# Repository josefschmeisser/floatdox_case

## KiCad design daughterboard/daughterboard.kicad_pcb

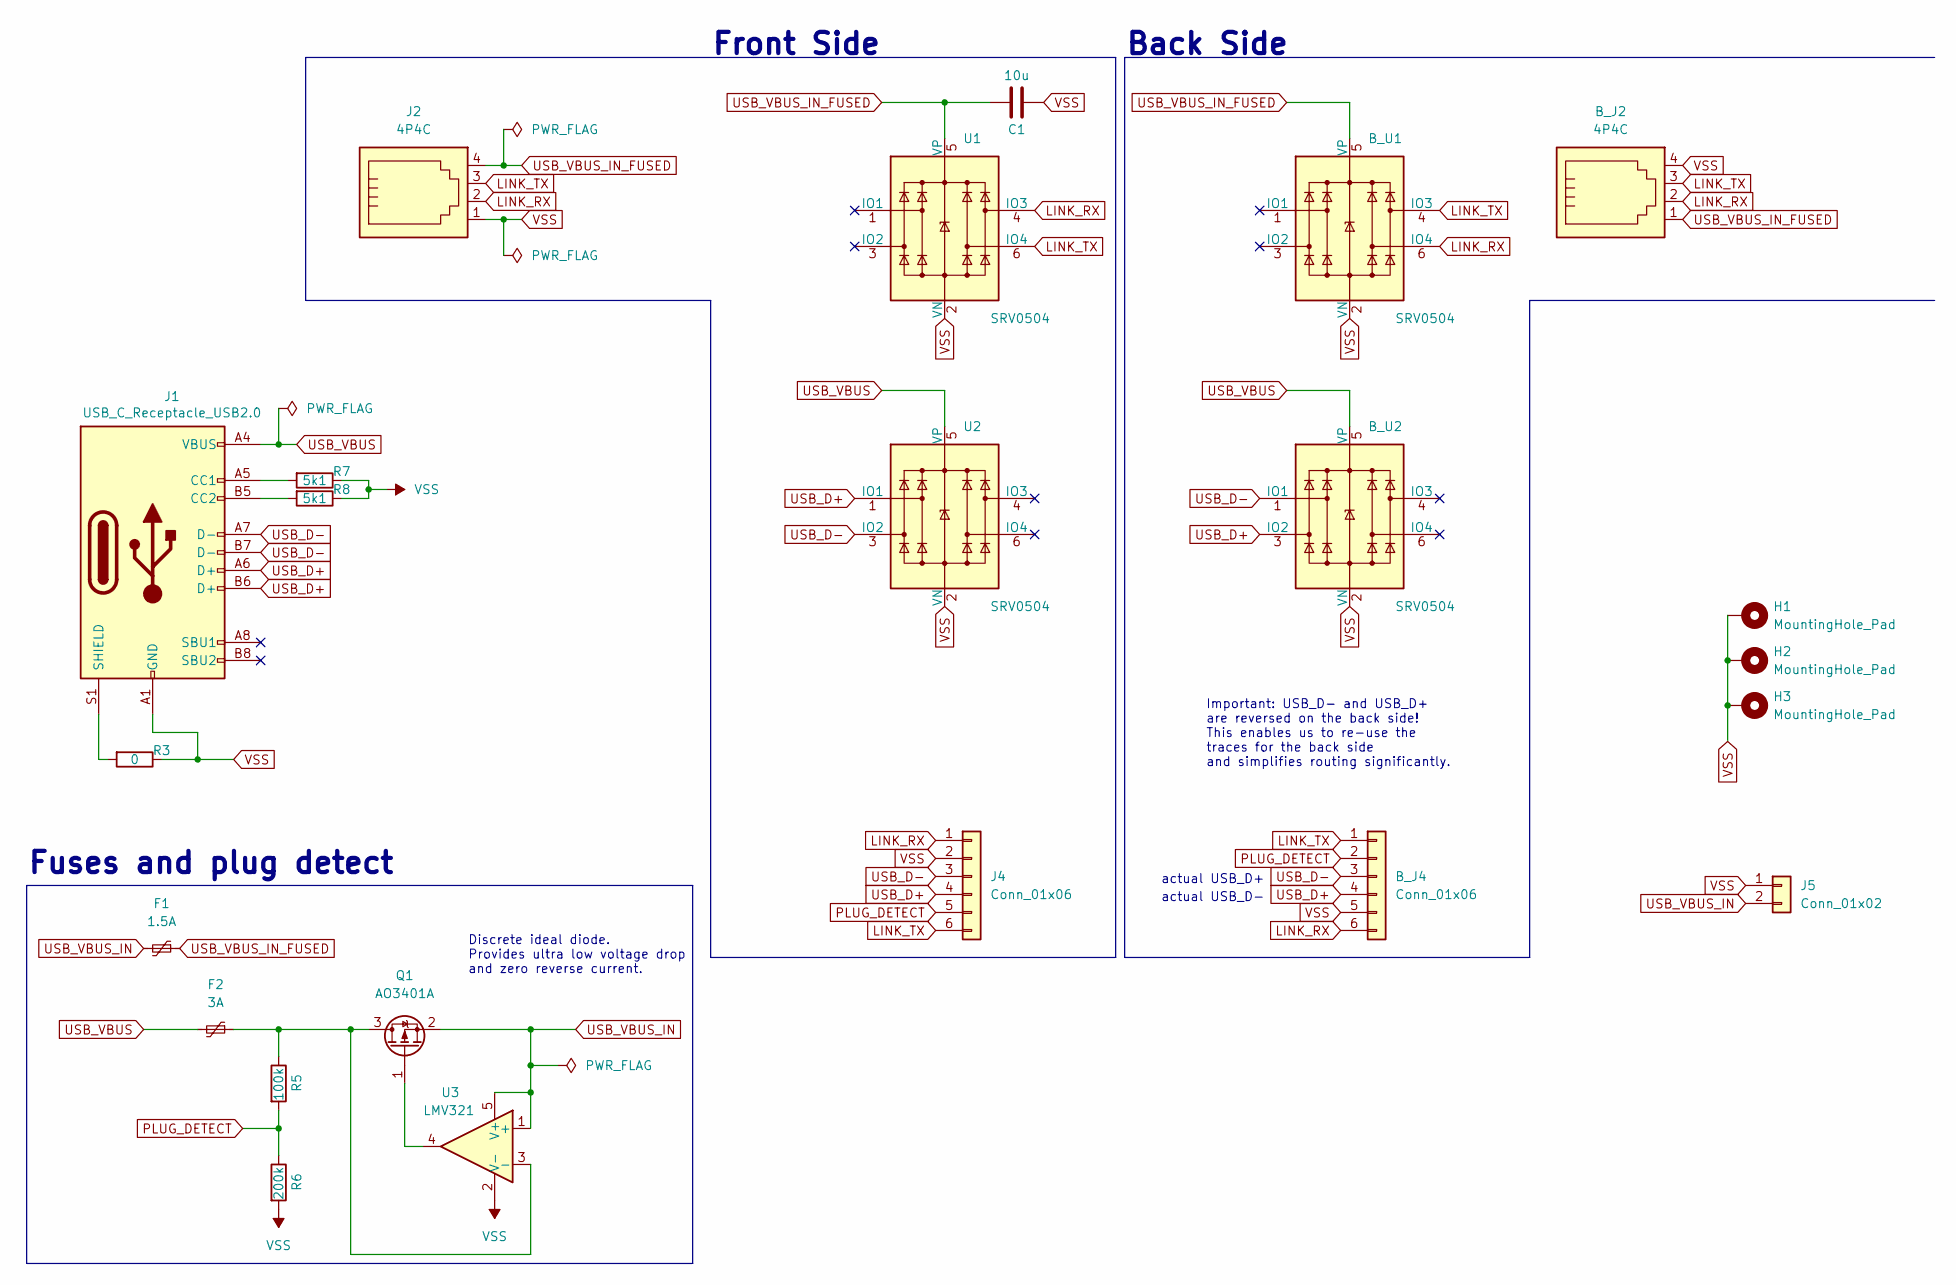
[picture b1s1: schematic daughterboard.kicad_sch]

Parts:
B_J2: 4P4C; RJ9_Molex_0855025005; LCSC PN TODO
B_J4: Conn_01x06; JST_ZH_S6B-ZR-SM4A-TF; LCSC PN C265070
B_U1, B_U2: SRV0504; SOT-23-6; LCSC PN C384888
C1: 10u; SMD-0603_Flippable; LCSC PN C19702
F1: 1.5A; Fuse_1206_3216Metric_Flippable; LCSC PN C70081
F2: 3A; Fuse_1206_3216Metric_Flippable; LCSC PN C70085
H1, H2, H3: MountingHole_Pad; MountingHole_2.2mm_M2_Pad_Via
J1: USB_C_Receptacle_USB2.0; USB_C_Receptacle_HRO_TYPE-C-31-M-12_Flippable; LCSC PN C168688
J2: 4P4C; RJ9_Molex_0855025005; LCSC PN TODO
J4: Conn_01x06; JST_ZH_S6B-ZR-SM4A-TF; LCSC PN C157931
J5: Conn_01x02; JST_XH_S2B-XH-A_1x02_P2.50mm_Horizontal; LCSC PN C157931
Q1: AO3401A; SOT-23_Flippable; LCSC PN C15127
R3: 0; SMD-0603_Flippable; LCSC PN C21189
R5: 100k; SMD-0603_Flippable; LCSC PN C25803
R6: 200k; SMD-0603_Flippable; LCSC PN C25811
R7, R8: 5k1; SMD-0603_Flippable; LCSC PN C23186
U1, U2: SRV0504; SOT-23-6; LCSC PN C384888
U3: LMV321; SOT-23-5_Flippable; LCSC PN C90297

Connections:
LINK_RX: B_J2.2, B_J4.6, B_U1.6 (IO4), J2.2, J4.1, U1.4 (IO3)
LINK_TX: B_J2.3, B_J4.1, B_U1.4 (IO3), J2.3, J4.6, U1.6 (IO4)
unnamed: F2.1, Q1.3 (D), R5.1, U3.3 (-)
unnamed: J1.A5 (CC1), R7.2
unnamed: J1.B5 (CC2), R8.2
unnamed: J1.S1 (SHIELD), R3.2
unnamed: Q1.1 (G), U3.4
PLUG_DETECT: B_J4.2, J4.5, R5.2, R6.1
USB_D+: B_J4.4, B_U2.3 (IO2), J1.A6 (D+), J1.B6 (D+), J4.4, U2.1 (IO1)
USB_D-: B_J4.3, B_U2.1 (IO1), J1.A7 (D-), J1.B7 (D-), J4.3, U2.3 (IO2)
USB_VBUS: B_U2.5 (VP), F2.2, J1.A4 (VBUS), J1.A9 (VBUS), J1.B4 (VBUS), J1.B9 (VBUS), U2.5 (VP)
USB_VBUS_IN: F1.2, J5.2, Q1.2 (S), U3.1 (+), U3.5 (V+)
USB_VBUS_IN_FUSED: B_J2.1, B_U1.5 (VP), C1.1, F1.1, J2.4, U1.5 (VP)
VSS: B_J2.4, B_J4.5, B_U1.2 (VN), B_U2.2 (VN), C1.2, H1.1, H2.1, H3.1, J1.A1 (GND), J1.A12 (GND), J1.B1 (GND), J1.B12 (GND), J2.1, J4.2, J5.1, R3.1, R6.2, R7.1, R8.1, U1.2 (VN), U2.2 (VN), U3.2 (V-)

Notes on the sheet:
Fuses and plug detect
Front Side
actual USB_D-
Important: USB_D- and USB_D+ are reversed on the back side! This enables us to re-use the traces for the back side and simplifies routing significantly.
actual USB_D+
Back Side
Discrete ideal diode. Provides ultra low voltage drop and zero reverse current.

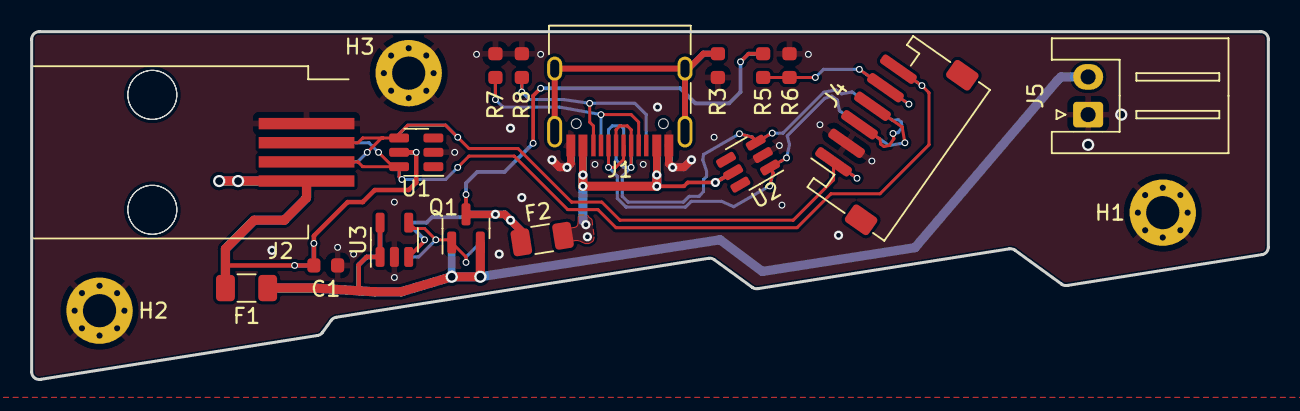
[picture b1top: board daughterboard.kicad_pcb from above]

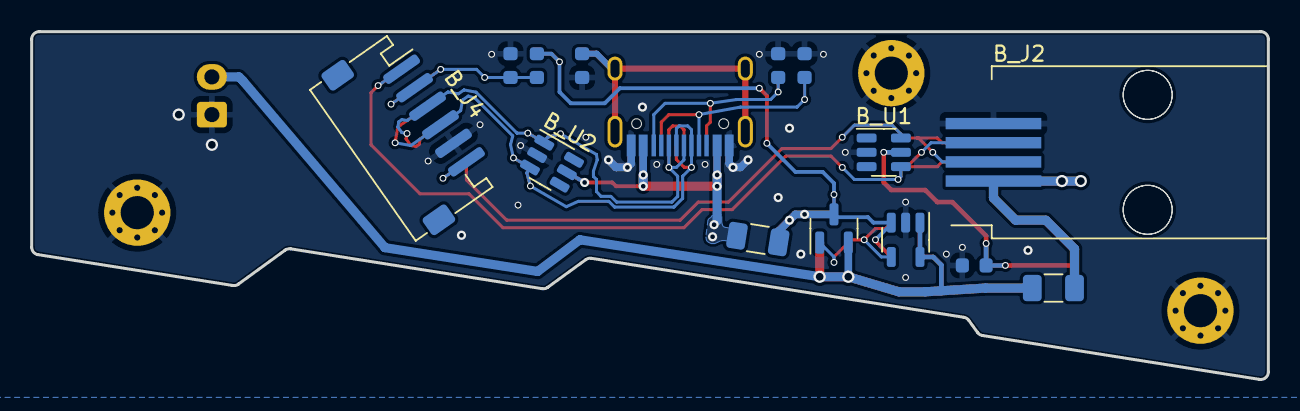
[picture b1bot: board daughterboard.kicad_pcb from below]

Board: 2 copper layers, 82.0 x 23.1 mm, 23 parts (4 on the bottom side), 14 nets.

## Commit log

2024-10-22 add license
